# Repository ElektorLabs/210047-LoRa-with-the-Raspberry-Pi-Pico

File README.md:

# 210047 LoRa with the Raspberry Pi Pico

## Software

 MicroPython scripts for the Raspberry Pi Pico, to get LoRaWAN
 uses a RFM95 module 

## Hardware 
 First version of a Raspberry Pi Pico project adding a RFM95 , DS18B20 and a recharable power supply to it.
 Done with KiCad and work in progress, so use at your own risk.

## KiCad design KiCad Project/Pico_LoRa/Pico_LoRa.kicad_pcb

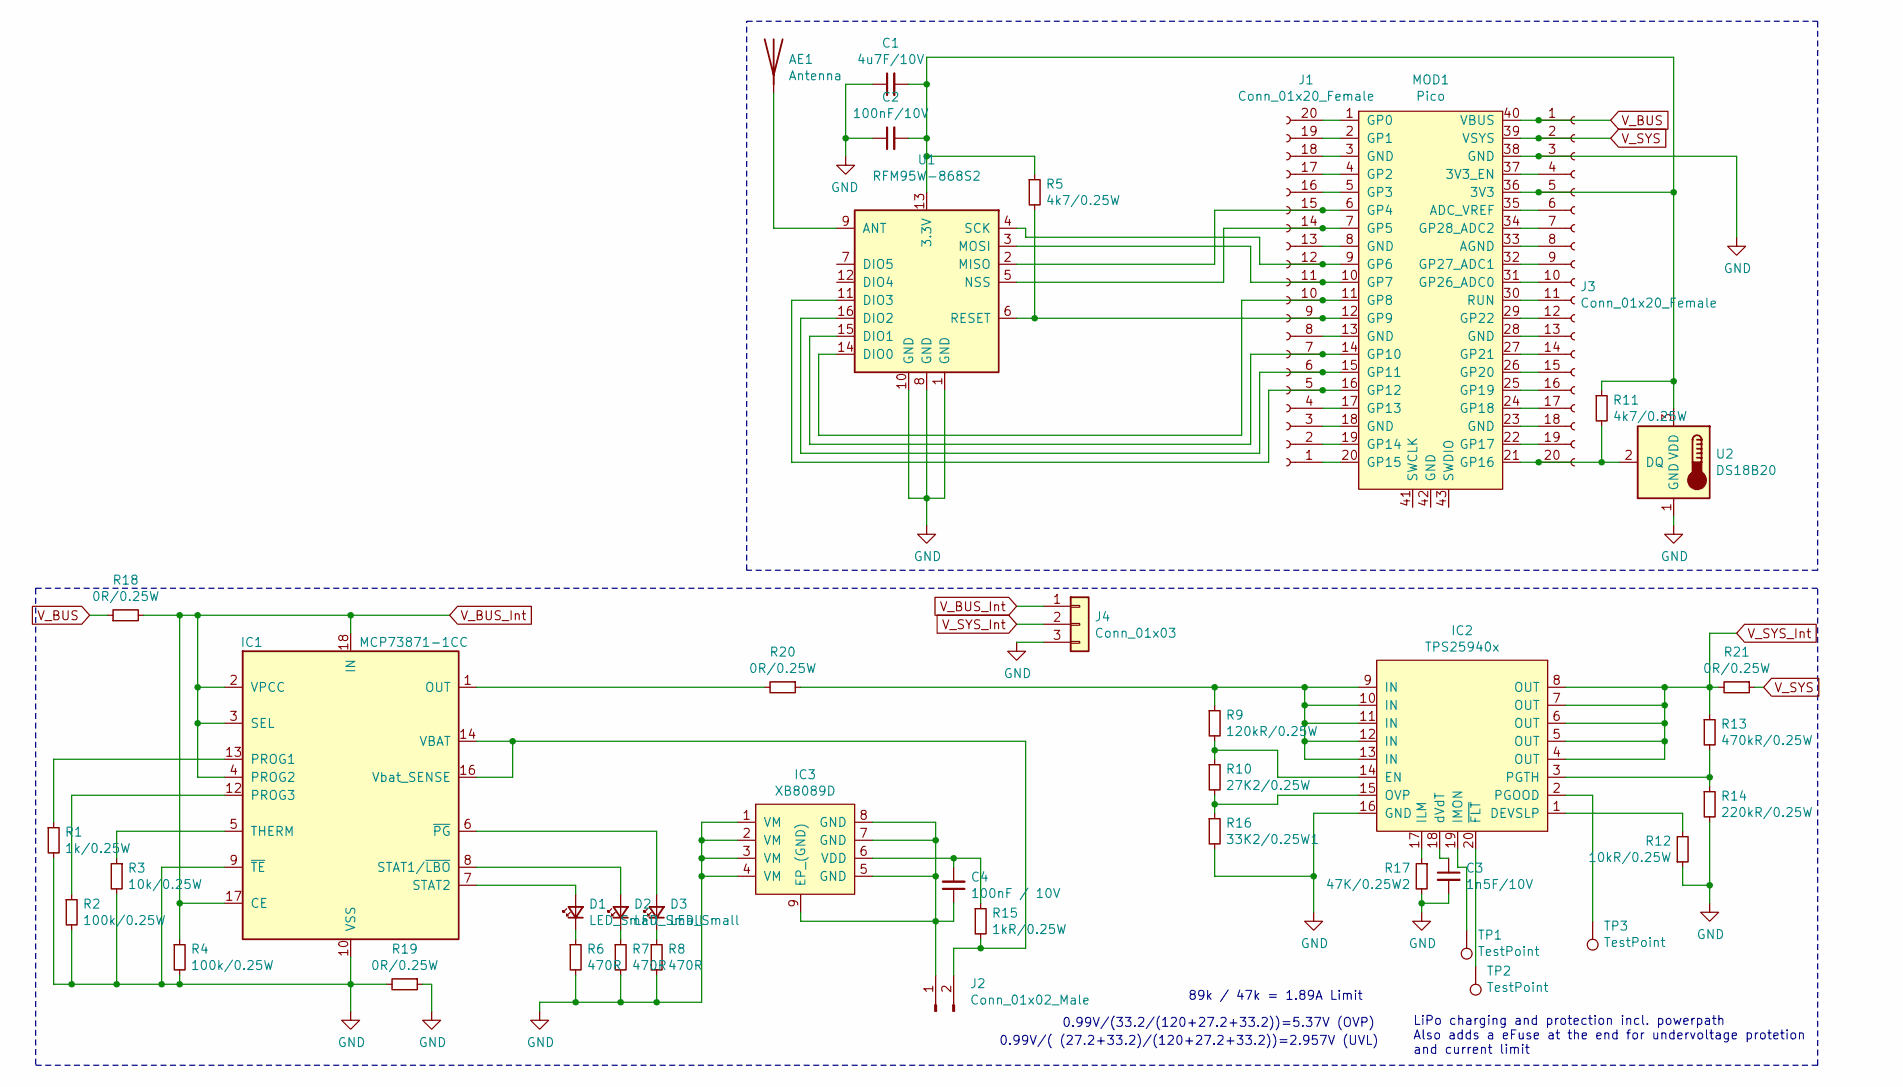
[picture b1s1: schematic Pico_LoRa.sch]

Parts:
AE1: Antenna; PinHeader_1x01_P2.54mm_Vertical
C1: 4u7F/10V; C_0805_2012Metric_Pad1.18x1.45mm_HandSolder
C2: 100nF/10V; C_0805_2012Metric_Pad1.18x1.45mm_HandSolder
C3: 1n5F/10V; C_0805_2012Metric_Pad1.18x1.45mm_HandSolder
C4: 100nF / 10V; C_0805_2012Metric_Pad1.18x1.45mm_HandSolder
D1, D2, D3: LED_Small; LED_0805_2012Metric_Pad1.15x1.40mm_HandSolder
IC1: MCP73871-1CC; QFN-20-1EP_4x4mm_P0.5mm_EP2.5x2.5mm
IC2: TPS25940x; TI_WQFN_20_EP
IC3: XB8089D
J1, J3: Conn_01x20_Female; PinSocket_1x20_P2.54mm_Vertical
J2: Conn_01x02_Male; PinSocket_1x02_P2.54mm_Vertical
J4: Conn_01x03; PinHeader_1x03_P2.54mm_Vertical
MOD1: Pico; RPi_Pico_SMD_TH
R1: 1k/0.25W; R_0805_2012Metric_Pad1.20x1.40mm_HandSolder
R2, R4: 100k/0.25W; R_0805_2012Metric_Pad1.20x1.40mm_HandSolder
R3: 10k/0.25W; R_0805_2012Metric_Pad1.20x1.40mm_HandSolder
R5, R11: 4k7/0.25W; R_0805_2012Metric_Pad1.20x1.40mm_HandSolder
R6, R7, R8: 470R; R_0805_2012Metric_Pad1.20x1.40mm_HandSolder
R9: 120kR/0.25W; R_0805_2012Metric_Pad1.20x1.40mm_HandSolder
R10: 27K2/0.25W; R_0805_2012Metric_Pad1.20x1.40mm_HandSolder
R12: 10kR/0.25W; R_0805_2012Metric_Pad1.20x1.40mm_HandSolder
R13: 470kR/0.25W; R_0805_2012Metric_Pad1.20x1.40mm_HandSolder
R14: 220kR/0.25W; R_0805_2012Metric_Pad1.20x1.40mm_HandSolder
R15: 1kR/0.25W; R_0805_2012Metric_Pad1.20x1.40mm_HandSolder
R16: 33K2/0.25W1; R_0805_2012Metric_Pad1.20x1.40mm_HandSolder
R17: 47K/0.25W2; R_0805_2012Metric_Pad1.20x1.40mm_HandSolder
R18, R19, R20, R21: 0R/0.25W; R_0805_2012Metric_Pad1.20x1.40mm_HandSolder
TP1, TP2, TP3: TestPoint; TestPoint_Pad_D1.0mm
U1: RFM95W-868S2; HOPERF_RFM9XW_SMD
U2: DS18B20; TO-92_Inline

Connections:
GND: C1.1, C2.1, C3.2, IC1.9 (~TE), IC1.10 (VSS), IC1.11 (VSS), IC1.21 (VSS), IC2.16 (GND), IC3.1 (VM), IC3.2 (VM), IC3.3 (VM), IC3.4 (VM), J3.3, J4.3, MOD1.38 (GND), R1.2, R2.2, R3.2, R4.2, R6.2, R7.2, R8.2, R12.1, R14.2, R16.2, R17.2, R19.1, R19.2, U1.1 (GND), U1.8 (GND), U1.10 (GND), U2.1 (GND)
unnamed: AE1.1, U1.9 (ANT)
unnamed: C1.2, C2.2, J3.5, MOD1.36 (3V3), R5.1, R11.1, U1.13 (3.3V), U2.3 (VDD)
unnamed: C3.1, IC2.18 (dVdT)
unnamed: C4.1, IC3.5 (GND), IC3.7 (GND), IC3.8 (GND), IC3.9 (EP_(GND)), J2.1
unnamed: C4.2, IC3.6 (VDD), R15.1
unnamed: D1.1 (K), R6.1
unnamed: D1.2 (A), IC1.7 (STAT2)
unnamed: D2.1 (K), R7.1
unnamed: D2.2 (A), IC1.8 (STAT1/~LBO~)
unnamed: D3.1 (K), R8.1
unnamed: D3.2 (A), IC1.6 (~PG~)
unnamed: IC1.1 (OUT), IC1.20 (OUT), R20.2
unnamed: IC1.5 (THERM), R3.1
unnamed: IC1.12 (PROG3), R2.1
unnamed: IC1.13 (PROG1), R1.1
unnamed: IC1.14 (VBAT), IC1.15 (VBAT), IC1.16 (Vbat_SENSE), J2.2, R15.2
unnamed: IC2.1 (DEVSLP), R12.2
unnamed: IC2.2 (PGOOD), TP3.1
unnamed: IC2.3 (PGTH), R13.2, R14.1
unnamed: IC2.9 (IN), IC2.10 (IN), IC2.11 (IN), IC2.12 (IN), IC2.13 (IN), R9.1, R20.1
unnamed: IC2.14 (EN), R9.2, R10.1
unnamed: IC2.15 (OVP), R10.2, R16.1
unnamed: IC2.17 (ILM), R17.1
unnamed: IC2.19 (IMON), TP1.1
unnamed: IC2.20 (~FLT), TP2.1
unnamed: J1.1, MOD1.20 (GP15)
unnamed: J1.2, MOD1.19 (GP14)
unnamed: J1.3, MOD1.18 (GND)
unnamed: J1.4, MOD1.17 (GP13)
unnamed: J1.5, MOD1.16 (GP12), U1.11 (DIO3)
unnamed: J1.6, MOD1.15 (GP11), U1.16 (DIO2)
unnamed: J1.7, MOD1.14 (GP10), U1.15 (DIO1)
unnamed: J1.8, MOD1.13 (GND)
unnamed: J1.9, MOD1.12 (GP9), R5.2, U1.6 (RESET)
unnamed: J1.10, MOD1.11 (GP8), U1.14 (DIO0)
unnamed: J1.11, MOD1.10 (GP7), U1.3 (MOSI)
unnamed: J1.12, MOD1.9 (GP6), U1.4 (SCK)
unnamed: J1.13, MOD1.8 (GND)
unnamed: J1.14, MOD1.7 (GP5), U1.5 (NSS)
unnamed: J1.15, MOD1.6 (GP4), U1.2 (MISO)
unnamed: J1.16, MOD1.5 (GP3)
unnamed: J1.17, MOD1.4 (GP2)
unnamed: J1.18, MOD1.3 (GND)
unnamed: J1.19, MOD1.2 (GP1)
unnamed: J1.20, MOD1.1 (GP0)
unnamed: J3.4, MOD1.37 (3V3_EN)
unnamed: J3.6, MOD1.35 (ADC_VREF)
unnamed: J3.7, MOD1.34 (GP28_ADC2)
unnamed: J3.8, MOD1.33 (AGND)
unnamed: J3.9, MOD1.32 (GP27_ADC1)
unnamed: J3.10, MOD1.31 (GP26_ADC0)
unnamed: J3.11, MOD1.30 (RUN)
unnamed: J3.12, MOD1.29 (GP22)
unnamed: J3.13, MOD1.28 (GND)
unnamed: J3.14, MOD1.27 (GP21)
unnamed: J3.15, MOD1.26 (GP20)
unnamed: J3.16, MOD1.25 (GP19)
unnamed: J3.17, MOD1.24 (GP18)
unnamed: J3.18, MOD1.23 (GND)
unnamed: J3.19, MOD1.22 (GP17)
unnamed: J3.20, MOD1.21 (GP16), R11.2, U2.2 (DQ)
V_BUS: J3.1, MOD1.40 (VBUS), R18.1
V_BUS_Int: IC1.2 (VPCC), IC1.3 (SEL), IC1.4 (PROG2), IC1.17 (CE), IC1.18 (IN), IC1.19 (IN), J4.1, R4.1, R18.2
V_SYS: J3.2, MOD1.39 (VSYS), R21.1
V_SYS_Int: IC2.4 (OUT), IC2.5 (OUT), IC2.6 (OUT), IC2.7 (OUT), IC2.8 (OUT), J4.2, R13.1, R21.2

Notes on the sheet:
LiPo charging and protection incl. powerpath Also adds a eFuse at the end for undervoltage protetion and current limit
0.99V/(33.2/(120+27.2+33.2))=5.37V (OVP)
0.99V/( (27.2+33.2)/(120+27.2+33.2))=2.957V (UVL)
89k / 47k = 1.89A Limit

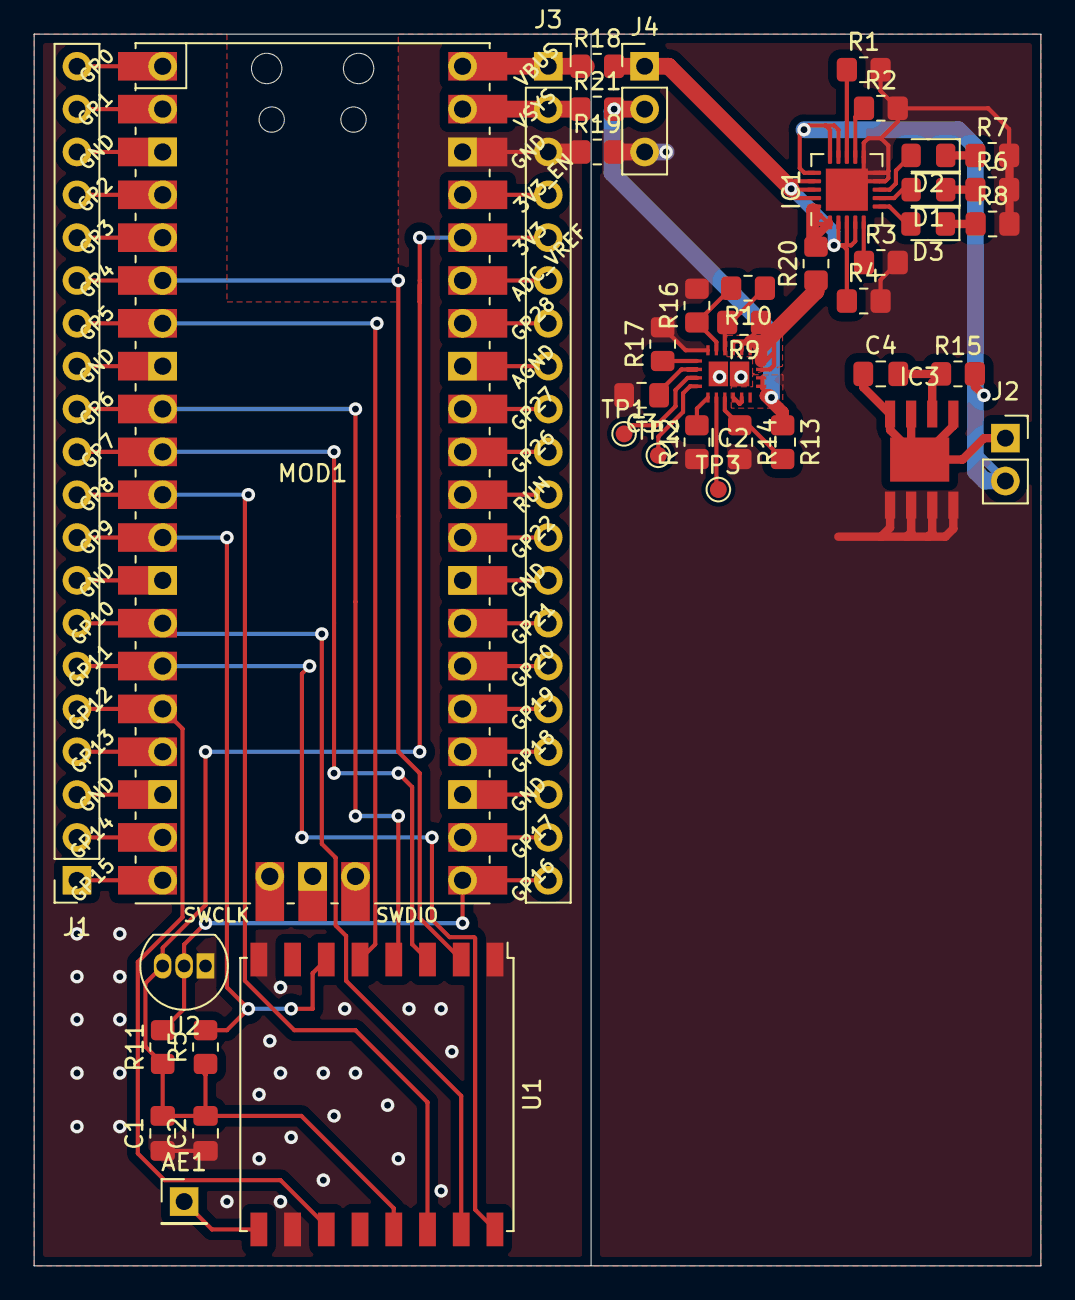
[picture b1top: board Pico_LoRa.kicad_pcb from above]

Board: 2 copper layers, 59.7 x 73.0 mm, 42 parts (0 on the bottom side), 66 nets.

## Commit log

2021-02-24 first commit
    first commit
2021-02-24 added README
    added file
2021-07-21 Added Node Red Flow
    Added Node Red Flow
2022-06-29 Fix for issue #1
    Fixed wrong RST assignment in ulora.py
